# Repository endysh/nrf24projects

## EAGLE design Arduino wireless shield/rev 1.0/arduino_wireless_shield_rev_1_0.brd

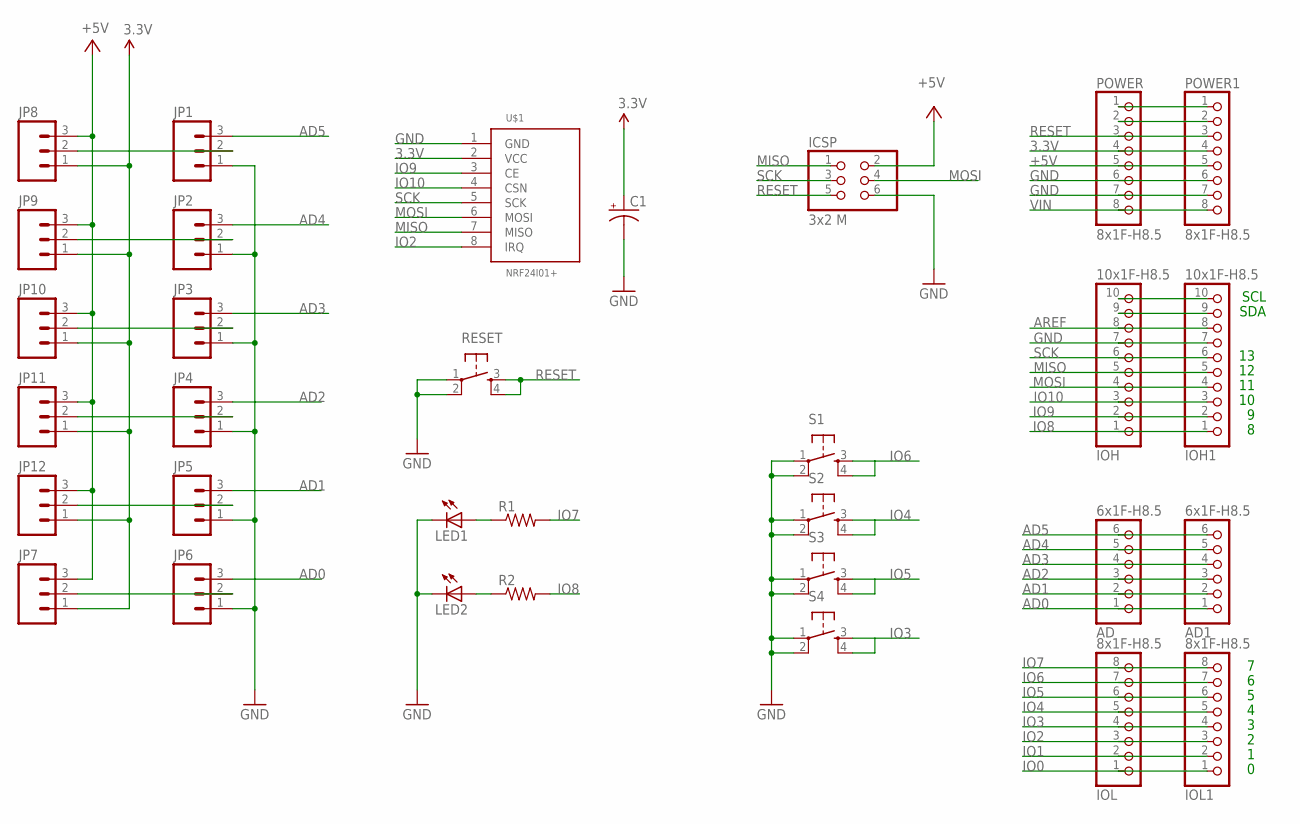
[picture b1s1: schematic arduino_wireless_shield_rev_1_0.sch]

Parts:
AD, AD1: 6x1F-H8.5; 1X06
C1: CPOL-USTT2D7; TT2D7
ICSP: 3x2 M; 2X03
IOH, IOH1: 10x1F-H8.5; 1X10
IOL, IOL1: 8x1F-H8.5; 1X08
JP1, JP2, JP3, JP4, JP5, JP6, JP7, JP8, JP9, JP10, JP11, JP12: M03PTH; 1X03
LED1, LED2: LED5MM
POWER, POWER1: 8x1F-H8.5; 1X08
R1, R2: RESISTORPTH-1/4W; AXIAL-0.4
RESET: TAC_SWITCHPTH; TACTILE-PTH
S1, S2, S3, S4: TAC_SWITCHPTH; TACTILE-PTH
U$1: NRF24L01+_MODULE; NRF24L01+MODULE

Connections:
3.3V: C1.+, JP7.1, JP8.1, JP9.1, JP10.1, JP11.1, JP12.1, POWER.4, POWER1.4, U$1.2 (VCC)
+5V: ICSP.2, JP7.3, JP8.3, JP9.3, JP10.3, JP11.3, JP12.3, POWER.5, POWER1.5
AD0: AD.1, AD1.1, JP6.3
AD1: AD.2, AD1.2, JP5.3
AD2: AD.3, AD1.3, JP4.3
AD3: AD.4, AD1.4, JP3.3
AD4: AD.5, AD1.5, JP2.3
AD5: AD.6, AD1.6, JP1.3
AREF: IOH.8, IOH1.8
GND: C1.-, ICSP.6, IOH.7, IOH1.7, JP1.1, JP2.1, JP3.1, JP4.1, JP5.1, JP6.1, LED1.K (C), LED2.K (C), POWER.6, POWER.7, POWER1.6, POWER1.7, RESET.1, RESET.2, S1.1, S1.2, S2.1, S2.2, S3.1, S3.2, S4.1, S4.2, U$1.1 (GND)
IO0: IOL.1, IOL1.1
IO1: IOL.2, IOL1.2
IO2: IOL.3, IOL1.3, U$1.8 (IRQ)
IO3: IOL.4, IOL1.4, S4.3, S4.4
IO4: IOL.5, IOL1.5, S2.3, S2.4
IO5: IOL.6, IOL1.6, S3.3, S3.4
IO6: IOL.7, IOL1.7, S1.3, S1.4
IO7: IOL.8, IOL1.8, R1.P$2 (2)
IO8: IOH.1, IOH1.1, R2.P$2 (2)
IO9: IOH.2, IOH1.2, U$1.3 (CE)
IO10: IOH.3, IOH1.3, U$1.4 (CSN)
MISO: ICSP.1, IOH.5, IOH1.5, U$1.7 (MISO)
MOSI: ICSP.4, IOH.4, IOH1.4, U$1.6 (MOSI)
unnamed: POWER.1, POWER1.1
unnamed: POWER.2, POWER1.2
unnamed: JP6.2, JP7.2
unnamed: LED2.A, R2.P$1 (1)
unnamed: LED1.A, R1.P$1 (1)
unnamed: IOH.10, IOH1.10
unnamed: IOH.9, IOH1.9
unnamed: JP5.2, JP12.2
unnamed: JP4.2, JP11.2
unnamed: JP3.2, JP10.2
unnamed: JP2.2, JP9.2
unnamed: JP1.2, JP8.2
RESET: ICSP.5, POWER.3, POWER1.3, RESET.3, RESET.4
SCK: ICSP.3, IOH.6, IOH1.6, U$1.5 (SCK)
VIN: POWER.8, POWER1.8

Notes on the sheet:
SDA
SCL

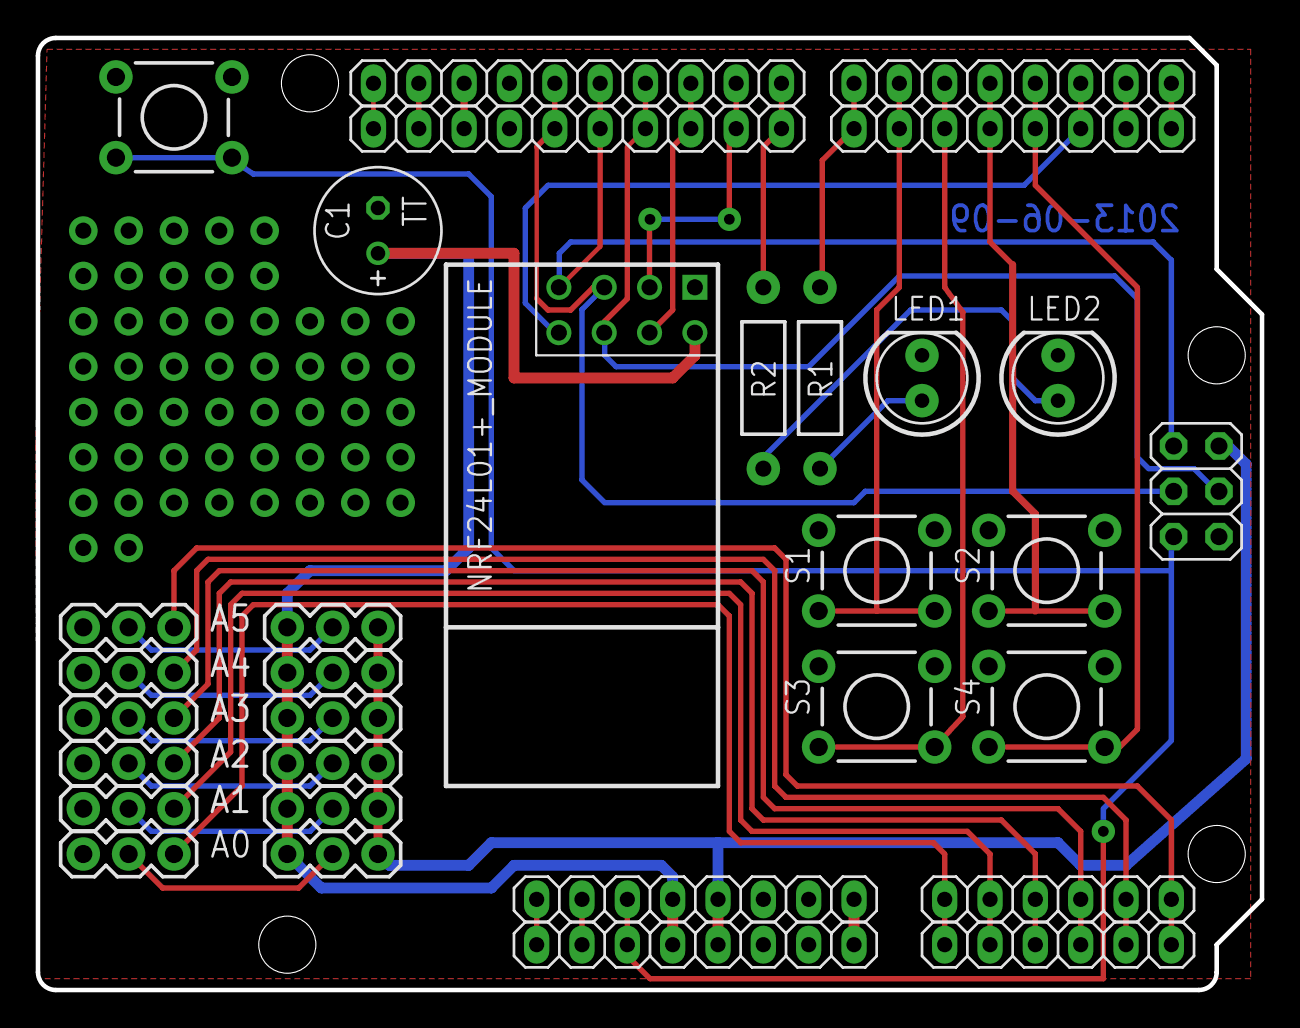
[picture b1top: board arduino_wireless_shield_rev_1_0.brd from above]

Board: 2 copper layers, 68.6 x 53.3 mm, 32 parts (0 on the bottom side), 38 nets.

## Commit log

2013-10-23 initial check-in

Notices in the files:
parts and their libraries:
SparkFun-Connectors: Licensing: CC v3.0 Share-Alike You are welcome to use this library for commercial purposes.
